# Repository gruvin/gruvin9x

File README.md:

# This project has been superseded by [openTx](https://github.com/opentx/opentx) and [Fr-Sky's Taranis](http://www.frsky-rc.com/product/pro.php?pro_id=113) RC Transmitter

## gruvin9x
### This outdated archive was recreated from [https://gruvin9x.googlecode.com/](https://gruvin9x.googlecode.com/) for historical reference and for the many still running gruvin9x boards or its dirivitives. A friendly shout out to you all! :-)

<h2>G9X v4.x BOARD (DISCONTINUED)</h2>

Why? Because there's much better things on the horizon -- we think. Trusted sources confirm the ongoing development of a Fr-Sky X9D transmitter, which we understand will be supporting open9x firmware form launch. The board will be ARM 32-bit based and is rumoured to be targeting sub-USD$100 retail -- complete with Fr-Sky 16-channel transmitter module, built in. If this all turns out to be true, then the complete radio will cost less than the G9X board (in the small qty's we can manage) whilst having all the same features and more. So we wait.

We simply don't know if demand for the G9X system will continue -- or not. Whilst orders seem to still be trickling in -- now even for blank boards (wow!) -- we don't expect that to last. Right or wrong, Gruvin made the choice, not to risk funds on another batch of G9X v4.2 boards. Was it the right choice? Have your say at <a href='http://9xforums.com/forum/viewforum.php?f=66'>9xforums.com</a>.<br>

<h2>We recommend openTx firmware</h2>

Please visit the [openTx website](http://open-tx.org) or the [openTx project on GitHub](https://github.com/opentx/opentx) for more information.

---

<h2>Gruvin9X Project Brief</h2>
<blockquote><i>First off, we especially wish to thank all the amazing original and ongoing work by</i>Thomas Husterer<i>of the <a href='http://code.google.com/p/th9x/'>th9x project</a>. A good number of other people have also contributed ideas, code and more to his, this and other related projects. THANK YOU all!</i></blockquote>

The gruvin9x project was originally forked from <code>er9x v1.1 r262</code> (<a href='http://code.google.com/p/er9x/source/browse/?r=262'>http://code.google.com/p/er9x/source/browse/?r=262</a>) which was based on a earlier version of the original th9x code. A huge amount effort was later put into the gruvin9x code base by contributor bsongis, of the <a href='http://open9x.googlecode.com'>open9x</a> and <a href='http://companion9x.googlecode.com'>companion9x</a> projects, which later became the sole point of focus for our custom hardware firmware support.<br>

<b>Highlights ...</b>
<ul><li><a href='wiki/About.md'>Project Wiki Documentation</a>
</li><li><a href='wiki/ReProgram.md'>Re-programming Your 9X Radio</a> -- firmware downloads, flashing, etc.<br>
</li><li><a href='wiki/PCB.md'>Custom Main Board Development</a> -- <b>upgrade your '9X controller board!</b></li></ul>

<h2>But what <i>is</i> it?</h2>
In short, this is an RC modeller/hacker's dream come true. We get to use your own custom firmware in our radios, adding features and making changes whenever we like and all (generally) at much lower cost than comparable commercial gear -- especially in terms of firmware features and programmability. We currently support any PPM transmitter module, with a focus on Fr-Sky two-way products, as well as DSM, DSM2 and DSMX 'retro-fitted' modules, usually salvaged from cheap 4-ch bind'n'fly models, as found on eBay.<br>

Open9x firmware is written and maintained by active RC modellers. It is mature, stable and very powerful. Based on th9x's 'multiplexer' implementation, it is arguably a little difficult to learn compared to other systems -- but is much more flexible. Open9x firmware is a significantly more powerful replacement for the comparatively simple default factory firmware that comes with the '9X radios.<br>

The <a href='wiki/PCB.md'>gruvin9x custom controller board</a> was developed using a larger version of the original Atmel AVR chip, to give us more RAM, firmware code space and more I/O connections for additional peripherals, such as telemetry data port, RTC/SD-card interface and more.<br>

If your existing transmitter doesn't do something you wish it would, chances are that open9x already does. If it doesn't, then put in a feature request and, if it makes sense to others, then the firmware will likely soon perform your new function.<br>

Both the open9x firmware and the companion9x (desktop) projects support our poplar <a href='wiki/PCB.md'>G9X v4 Custom Controller board</a>.<br>

<blockquote><i><b>Caveat</b>: Firmware is  half the story -- quality of hardware is not a given and should also be carefully considered. Whilst the build quality of most 9X radios seems just fine, there have been notable exceptions. We therefore strongly recommend that all firmware functions as well as internal radio soldering joints and physical gimbal assembly be carefully checked, before committing a 'cheap' 9X radio controlled aircraft to the skies. SAFETY FIRST!</i></blockquote>

The original <a href='http://code.google.com/p/th9x/'>TH9X project</a> was (and very much still is) about completely replacing the factory supplied operating system in the Turnigy/Eurgle/iMax/Fly-Sky/etc 9X Remote Control transmitter from China -- currently retailing for around USD$40 -- HOW, we do not know!<br>

From there, other projects then spawned (were forked forked) from TH9X, including ER9X and gruvin9x. More are likely to follow as different interest focuses emerge. In our case, the focus was originally on providing practical Fr-Sky telemetry support and more recently, the design and production of an <a href='PCB.md'>custom controller board</a>, to be a drop-in, upgrade replacement for the stock '9X system controller.<br>

There's more about gruvin9x on the <a href='wiki/About.md'>About</a> wiki page.<br>

<h3>Documentation</h3>

## Best Source of Information for openTx (June 2015)
Head over to <a href='http://www.open-tx.org/'>http://www.open-tx.org/</a>

For G9X hardware or historical information, please consult the <a href='wiki/About.md'>project wiki</a> in the first instance, as well as the <a href='firmware/doc'>firmwar/doc/ directory</a>  for ~~all currently available~~ archival gruvin9x documentation.<br>

<h3>Other '9X OS Replacements</h3>

There's also at least one other project taking on the same basic goal, but of completely different design and unrelated to the TH/ER/gruvin9X projects. It's named Radio Clone, can be found at <a href='http://radioclone.sourceforge.net/'>http://radioclone.sourceforge.net/</a> and is well worth checking out.<br>

<h2>Downloading gruvin9x Firmware and Flashing Your Radio</h2>

For details on installing new firmware into you Turnigy/iMax/Eurgle/etc 9X RC Radio, see the <a href='FlashGuide.md'>Flash Guide</a> wiki page.<br>

<h2>Getting the gruvin9x Source Code</h2>
See the <a href='wiki/CompilingFromSource.md'>Compiling from Source</a> wiki page.<br>

<h2>Get Involved!</h2>
An independent group maintain an, 'all things 9X' forum over at <a href='http://openrcforums.com'>http://openrcforums.com</a>. The forum caters to several different firmware projects, has a documentation wiki attached and is probably the most popular hang-out for '9X enthusiasts and much more besides. Frankly, it's freaking AMAZING! Go check it out.

## Gruvin9X Project Wiki</a>
(converted from old Google Code site)

* [About gruvin9x](wiki/About.md)
* [G9X Features](wiki/Features.md)
* [Screen Shots](wiki/Features.md)
* [General FAQ](wiki/FAQ.md)
* [Re-progamming Your Radio](wiki/ReProgram.md)
 * [Latest Stable Binaries](wiki/LatestRelease.md)
 * [Development Binaries](wiki/DevBinaries.md)
 * [Flashing Binary Versions](wiki/FlashGuide.md)
 * [Compiling from Source](wiki/CompilingFromSource.md)
 * [Make Options](wiki/MakeOptions.md)
* [Custom PCB (v4.x)](wiki/PCB.md)
 * [Custom Schematics](wiki/Circuitry.md)
 * [Build Your Own Board](wiki/PcbAssembly.md)
 * [SD Card Installation](wiki/SdcardBoard.md)
 * [9X Reference Data](wiki/TurnigyV2.md)
  * [Reference Images](wiki/ReferenceImages.md)
  * [V2 Circuit Schematic](wiki/SchematicV2.md)
  * *[v4.x Custom Board FAQ](wiki/V41FAQ.md)*
  * *[Get your own PCB made](wiki/PCBFab.md)*
* [USB Programmer](wiki/GProg.md)
* [Telemetry](wiki/Telemetry.md)
 * [Fr-Sky Support](wiki/FrSky.md)
 * [Fr-Sky Interfacing](wiki/FrskyInterfacing.md)
 * [Fr-Sky on your Mac](wiki/FrSkyTerminalOSX.md)
 * [Porting to ER9X](wiki/FrskyToER9X.md)
* [Donator Recognition](wiki/Recognition.md)
* [Random Notes](wiki/RandomNotes.md)
 * [AoA / LRI Notes/Ideas](wiki/AoA.md)
 * [Backlight Information](wiki/BackLight.md)
 * [eePe EEPROM file manager](wiki/eePe.md)
 * [PPM-in Compatibility (Hack)](wiki/PpmIn.md)
 * [Ni-Mh packs! Or not?](wiki/PowerCells.md)
 * [Repeat Delay](wiki/RepeatDelay.md)
 * [Speaker Upgrade](wiki/SpeakerReplacement.md)
 * [Voltage Averaging](wiki/VoltageAveraging.md)

## External Links
 * <a href="http://open-tx.org" rel="nofollow" style="font-size:2.0em"><b>openTx</b></a>
 * <a href='http://code.google.com/p/er9x/'>Original ER9X Project Home</a>
 * <a href='http://code.google.com/p/th9x/'>ORIGINAL, Original TH9X Project Home</a> "Respect!" :-D
 * <a href='http://sourceforge.net/apps/mediawiki/radioclone/'>Radio Clone Project</a> -- Something different and well worth checking out.
 * <a href='http://www.rcmodelreviews.com/tendollarbattery.shtml'>$10 Li-Ion Battery Pack Upgrade</a>
 * <a href="http://code.google.com/p/frsky-terminal/" rel="nofollow">FrSky Terminal (OS X)</a>
 * <a href="http://openpnp.org/wiki/index.php/Main_Page" rel="nofollow">OpenPnP</a>
 * <a href="http://www.rcgroups.com/forums/member.php?u=301789" rel="nofollow">Argos&#39;s &#39;9X Modd&#39;ing Blog</a>
 * <a href="http://code.google.com/p/er9x/" rel="nofollow">er9x</a>
 * <a href="http://code.google.com/p/th9x/" rel="nofollow">th9x</a>
 * <a href="http://radioclone.org/" rel="nofollow">radioclone</a>
 * <a href="http://9xforums.com/forum/" rel="nofollow">9X Forums</a>
 * <a href="http://companion9x.googlecode.com" rel="nofollow">companion9x</a>
 * <a href="http://www.fsf.org/about/what-is-free-software" rel="nofollow">What is &#39;free&#39; software?</a>

```

```
<h3>DISCLAIMER</h3>
Whilst the gruvin9x project owner(s) aim to provide as much help to as many Turnigy/iMax/Eurgle/etc '9X users as practical, any perceived enthusiasm on their part to lure people into using gruvin9x over any other version, would be erroneous. This project was originally created primarily for the author's own use -- and of course to 'give back' to the Open Source Community, as the <a href='http://www.gnu.org/licenses/gpl-2.0.html'>GNU General Public License (V2)</a> requests. Anyone is welcome to use this code according to said license, as is, where is and indeed to submit suggestions for changes, improvements, additions, etc. The author welcomes comments, constructive criticism, assistance and general feedback but accepts no responsibility for anything what-so-ever that use of any information contained on this website may or may not be claimed to cause. Use at your own risk. Any opinions offered by this internet resource are expressly, only opinions. (Any information claiming to be fact but not legally verified as fact in actuality, must of course be considered mere opinion, regardless of context.) All care is taken, but no responsibility is accepted for the level of accuracy of any information here or anywhere the author may post text, images, video, audio or other content. Any and all images, photographs, charts, lists or graphical representations of any kind are intended for educational or indicative purposes only and may or may not accurately represent any given subject, topic or fact at any given time. Indeed, any such depictions are subject to change at any time for any reason without notice. Any monetary figures, presented by whatever means, are for indicative, informational or educational purposes only and all such figures are subject to change at any time without notice. The use of sarcasm may or may not feature throughout this internet resource and other, related or linked media, and as such is intended purely as light-hearted humour. No responsibility is accepted for anything what-so-ever relating to perceived truths related to such believed communications. Reader/viewer/listener beware! Any views expressed by individuals other than project owner(s) may or may not agree with the projects goals, intentions or license and no responsibility is taken for any such view or views under any circumstance. Any views so interpreted as being those of the gruvin9x project owner(s) should be taken as potentially inaccurate and with the acceptance that any views, expressed or implied, are at all times subject to change without notice. This disclaimer falls within the above conditions, being itself subject to change at any time without notice. In light of the afore mentioned disclaimers, readers should take heed of the possibility that they may be, a) potentially crazy for reading this far in the first place and, b) that this disclaimer itself, though quite serious, is in part also intended for entertainment purposes. Etc, etc, blah blah. You know the drill. Love and peace to all! Now let's get on with it. :-D

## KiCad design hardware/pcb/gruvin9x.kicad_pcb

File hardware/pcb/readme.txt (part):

This PCB is a rework of Gruvin's V3.0 PCB to use the 100pin ATMega 2560. It was primarily done to enable the 
use of JTAG debugging and also to free up some pins for future fun. (Cam). Most of the work was done by Cam,
which has been just wonderful. Thanks Cam! (Gruvin)

============================
= Differences V4.1 to V4.2 =
============================

. All six (x4) push button switch holes enlarged to allow factory assembly, without manual adjustments to component legs.
. Changes made around Q2/Q3 pseudo RS-232 buffers to improve waveform profiles. R117 was added. Other resitros were reduced in value.

============================
= Differences V4.0 to V4.1 =
============================

. Switched PB0 and PB6 (PPM_OUT and IDL2_SW) assignment around to allow for a hardware PPM_OUT solution.
. After the above change we discovered we couldn't use PB0 (/SS) as an input for IDL2_SW.
  Unfortuantely when hardware SPI is used PB0 (/SS) can only be used for output, so we switched PB0 and PB4 (IDL2_SW and SD_CS)
  We now have:
  PIN         V4.0          V4.1            
  PB0 (/SS)   PPM_OUT   SD_CS
  PB4         SD_CS     IDL2_SW
  PB6 (OC1B)  IDL2_SW   PPM_OUT
. Switched the PPM_IN pull down resistor (R80) to pull up, worked better that way.
. Added components for a soft off switch.
. A few net name changes, Spare4 and Spare3 became Spare1\LED-BL-opt and Spare2\Vib-opt, and some net name changes for the soft off addition.
. In the move round for the soft off switch I mananged to add another decoupling cap around the CPU (C64)
. LED backlight fix. Needed NPN transistor to switch the P-FET.
. Changed the series LED backlight resistor to 200 ohms from 100 ohms, it looked better.
. Polarized caps are now indicated on the silkscreen.
. Jumper J4 graphic on schematic changed to show the config we are currently using as default.
. SDCard board connector moved to be more central, fits easier this way, at least for me.
. SDCard board also renamed to avoid confusion between the two versions.
. Up switch moved down 0.2mm.
. Addition of a fuse to the K5 LED back light header. We really need to implement a fuse to protect the whole board but without a
  total rip up it isn't going to happen. The fuse took the space of R103 which was removed, it was felt it was not needed.
. Broke the 3.3v rail out and a fused BATT+
. BOM also updated to reflect changes.

============================
= Differences V3.0 to V4.0 =
============================

Major
-----
* Replaced 64 pin AMega 2561 with 100 pin 2560
* Removed the 4066. Gruvin felt it bad for not offering enough protection to the CPU incase of user misconnects. So 
  it had to go. We now have seperate output buffer transistors to the module and the trainer jack. 
* Added a filter cap around Q1 to try and stop spurious switching when the buzzer sounds.
* Added voltage dividers to the four spare ADC pins, these may be used for monitoring individual Tx cell voltages,
  or anything, thought it useful to provide voltage dividers onboard.  
* Removed matrix for push buttons to make the board a true drop in replacement.  
* Added JTAG header
* Changed 10pin ISP header to 6pin
* Added breakout headers for spare pins, the whole of port L, half of port F (4x ADCs), and port H (inc. a second 
  serial port)
* Remaining 4 pins broken out to test point pads here and there.
* Switched the I2C interface to use hardware I2C pins 
* Switched the ADC usage from port F to port K to free up JTAG pins
* Added interfacing, connectors etc. for two rotary encoders as per Multiplex Evo sets (Hardware debouncing 
  with a little RC network). Added these on pins with interrupt triggers just in case needed.
* Switched pin for IDL_SW1 with Spare1 just to make routing easier
* Signals KEY_Y2 and KEY_Y3 have replaced the digital GND signals on the 9 pin headers that go to the pot gimbals 
  and trim switches. Because the trim buttons are now in a switch matrix, digi GND is no longer needed but the 
  matrix signals KEY_Y2 and KEY_Y3 are. On the V3 board these signals came out on a separate 2 pin header but this 
  can be avoided by doing this.
  ** NOTE ** The switch matrix requires a little mod/fix to operate correctly. On both of the horizontal 
  trim PCBs the trim switches are connected to analogue GND and not digi GND as they should be. In order for the 
  matrix to operate correctly we must remove the connection to analogue GND (by cutting PCB traces) and connect it 
  across to the digi GND point (now the KEY_Yn point) on the vertical trim board. 
  Pictures for this mod are in the .\Data Sheets\Switch Matrix Changes\ directory
* Added circuity to drive a vibrating motor for alarms etc. Have used a variable voltage regulator with enable signal
 (1.2v - 5.5v @ 500ma). This should hopefully allow a selection of motors to be used. Have also added a jumper 
 that either allows the Spare_2/PG5 signal or the PH3/OC4A PWM ouput to drive the enable on the regulator. I think 
 PWM control maybe an overkill but the option is there. Early indications show PS3 controller vibration motors 
 look good, they wedge in just fine in the bottom left of the back of the case (to the left of the battery 
 compartment). Got a copy ps3 wired controller from eBay for 6GBP. Contains two motors with differing weights, 
 either seems fine.
 Have tried driving the TPS77601 enable input with a PWM signal of around 250Hz while using one of the PS3 motors 
 and it seems fine. Have uped filter capacitors from the datasheet to try and keep noise generated low. The current
 combination of caps represent the lowest noise I have managed to get on both the motor side and the input side.
 
Minor
-----
* Added mounting holes into schematic so they don't disappear if you tell the netlist update to delete components 
  it can't find 
* Amalgamated the projects KiCAD libraries, and restructured their directories to better reflect KiCAD's own 
  library structure. (They confuse me less this way)

=======================================
= For reference V2.14 to V3.0 changes =
=======================================

* Change of speaker to PWM pin (provides MUCH cleaner tonnes, too.)
* Existing speaker output retained on original pin also -- this was in fact intended for vibrating motor (optionally.)
* Added breakout of I2C (This was more of a change to the SDcard interface)
* Added transistor in PPM_IN linen (Principal reason was for buffering/amplification.)
* Added breakout of Back Light signal, Vcc, and GND to 3 pin header
* Rearranged stick/trim switch interface wiring to remove awkward/stuffed-up cross-over bug. (This is a biggie!)
* Fix of reversed Collector and Emitter connections on Q3
* Small corrections to hole and switch positions. V2.14 was well within acceptable tolerances though.

=====================
= Component changes =
=====================
I renamed a few library parts that also exist in the standard KiCAD libraries to avoid confusion. 

These items are usually standard KiCAD parts that have been copied to the Gruvin library and tweaked a 
little for the needs of the project or to fix errors. These and only these parts have been given the 
_GRUVIN suffix on top of the normal KiCAD name. Original Gruvin library parts are just named normally.

I also edited a few parts.

The diffs are:

Footprints/Modules
------------------
SM0603        -> SM0603_GRUVIN         Silkscreen outline different
PIN_ARRAY_3X1 _> PIN_ARRAY_3X1_GRUVIN  Larger spacing and different 3D representation
PIN_ARRAY_3X2 -> PIN_ARRAY_3x2_GRUVIN  Bigger pads & didn't like 3D representation in std KiCAD part
PIN_ARRAY_4X2 -> PIN_ARRAY_4X2_GRUVIN  Bigger pads & no 3d rep
PIN_ARRAY_4X1 -> PIN_ARRAY_4X1_GRUVIN  Bigger pads & no 3d rep
PIN_ARRAY_5X2 -> PIN_ARRAY_5X2_GRUVIN  Bigger pads on 8 pins
SW_PUSH_6x4MM                          Bigger pads

Schematic components
--------------------
ATMEGA2560-A  -> ATMEGA2560-A_GRUVIN   Would you believe the standard KiCAD part has two power pins missing !
ATMEGA64      -> ATMEGA64_GRUVIN       Not sure, need to ask Bryan
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
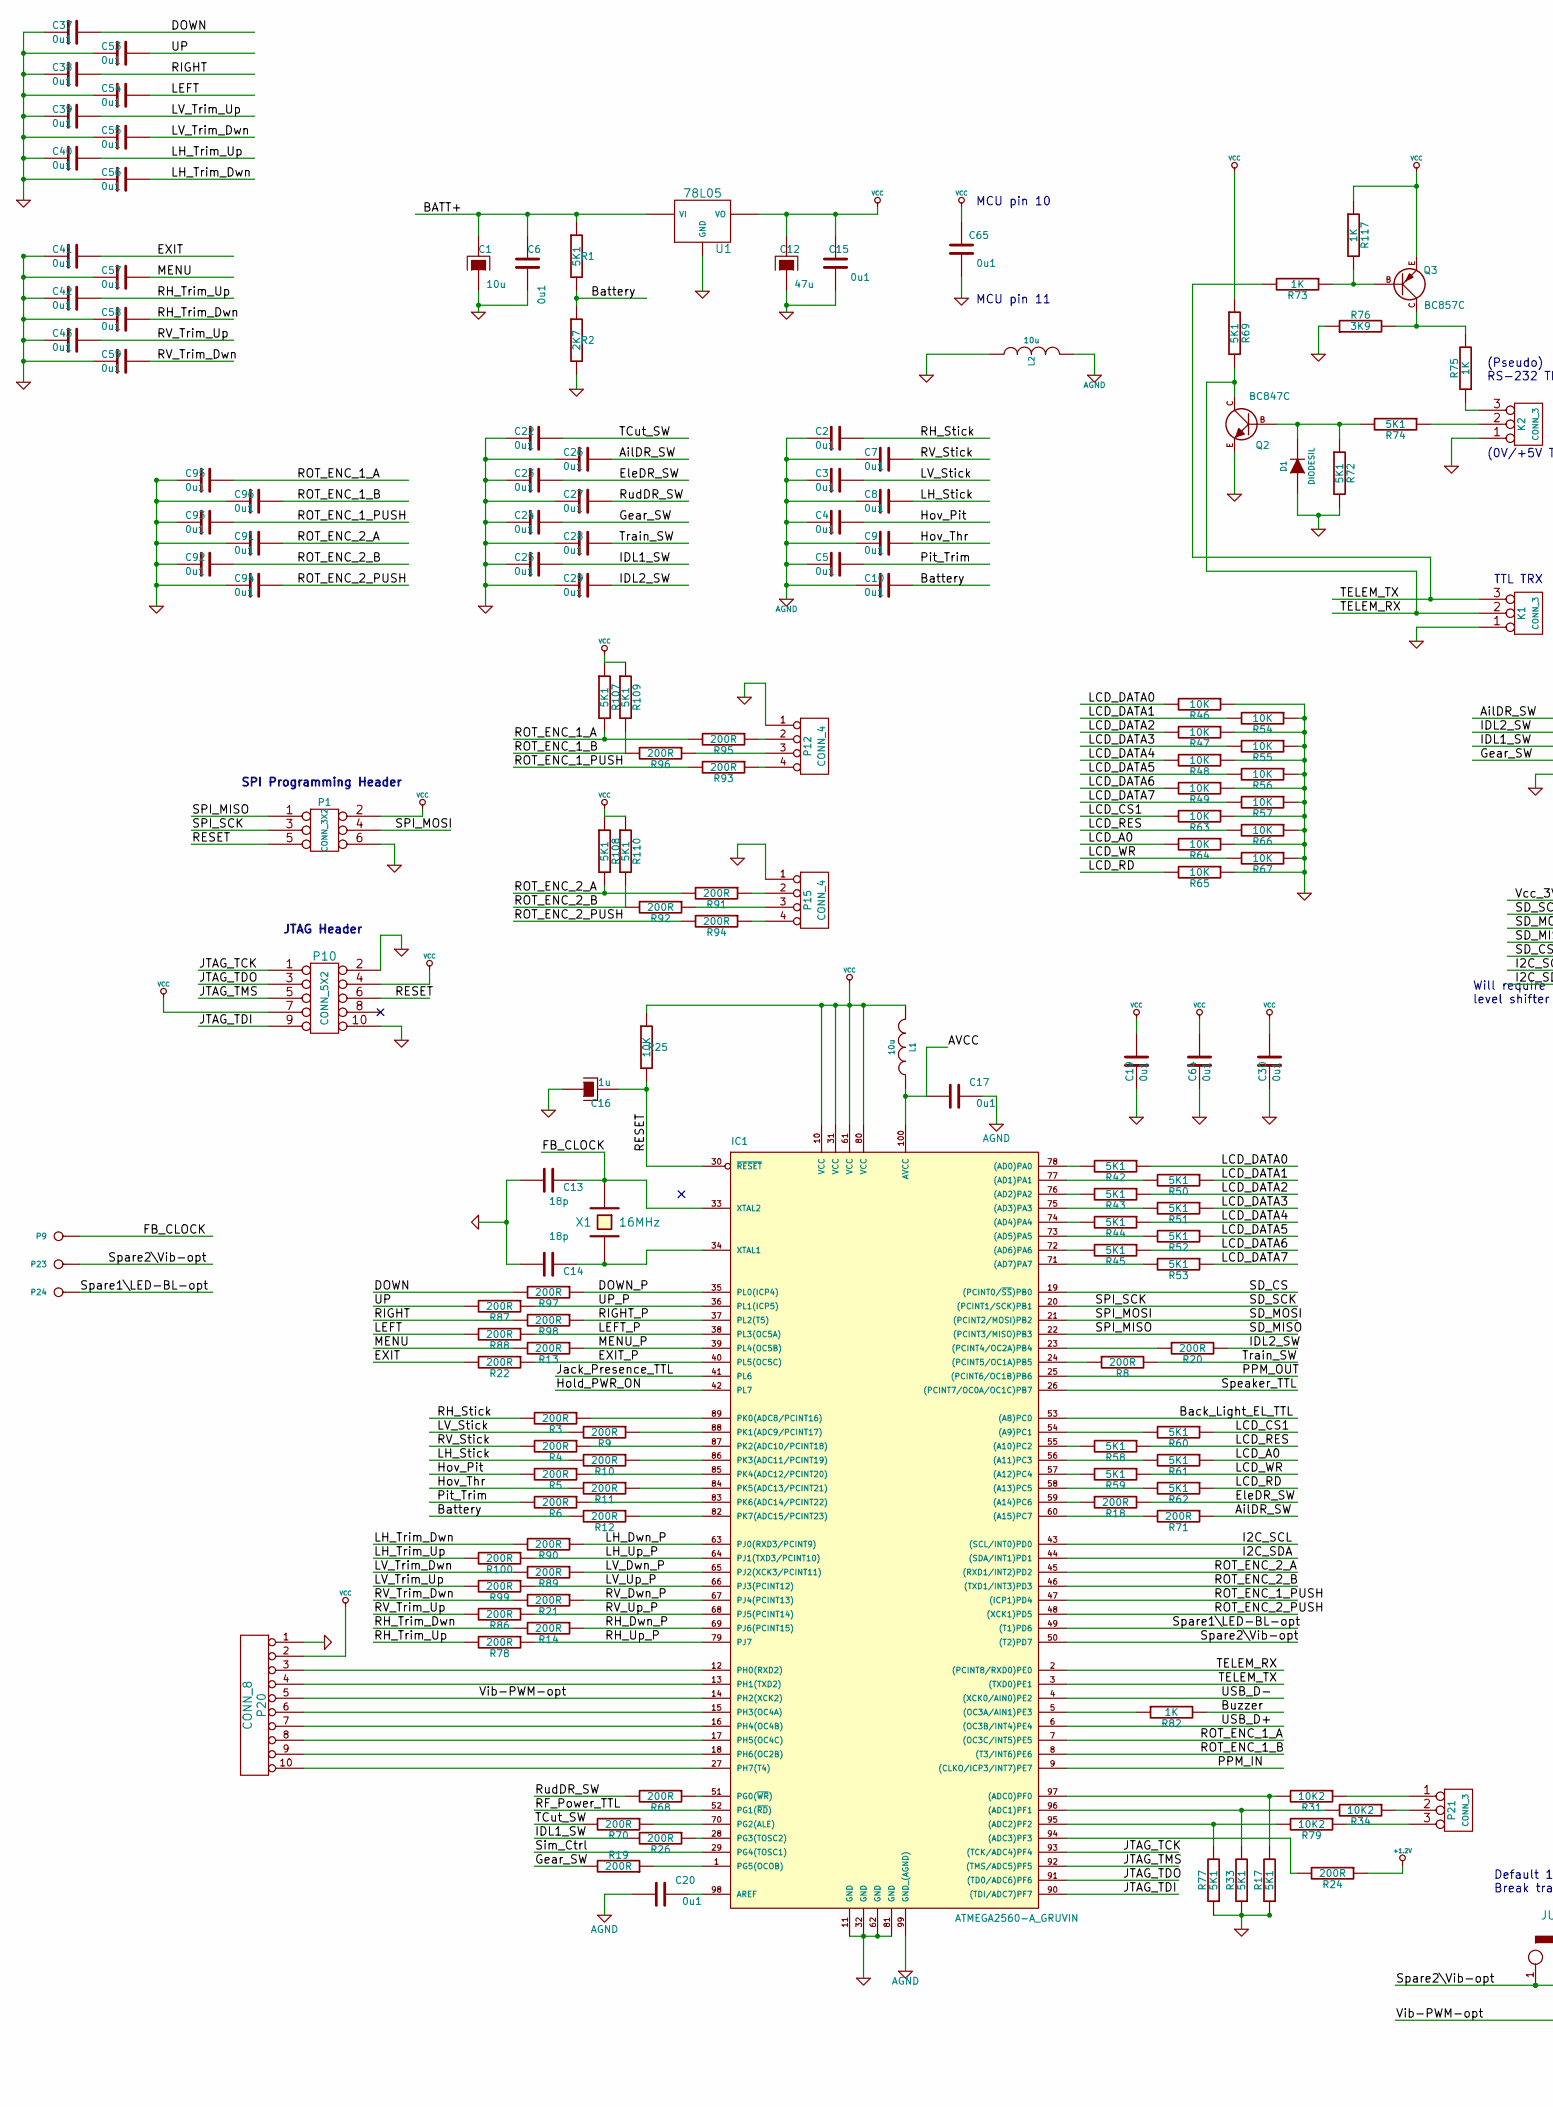
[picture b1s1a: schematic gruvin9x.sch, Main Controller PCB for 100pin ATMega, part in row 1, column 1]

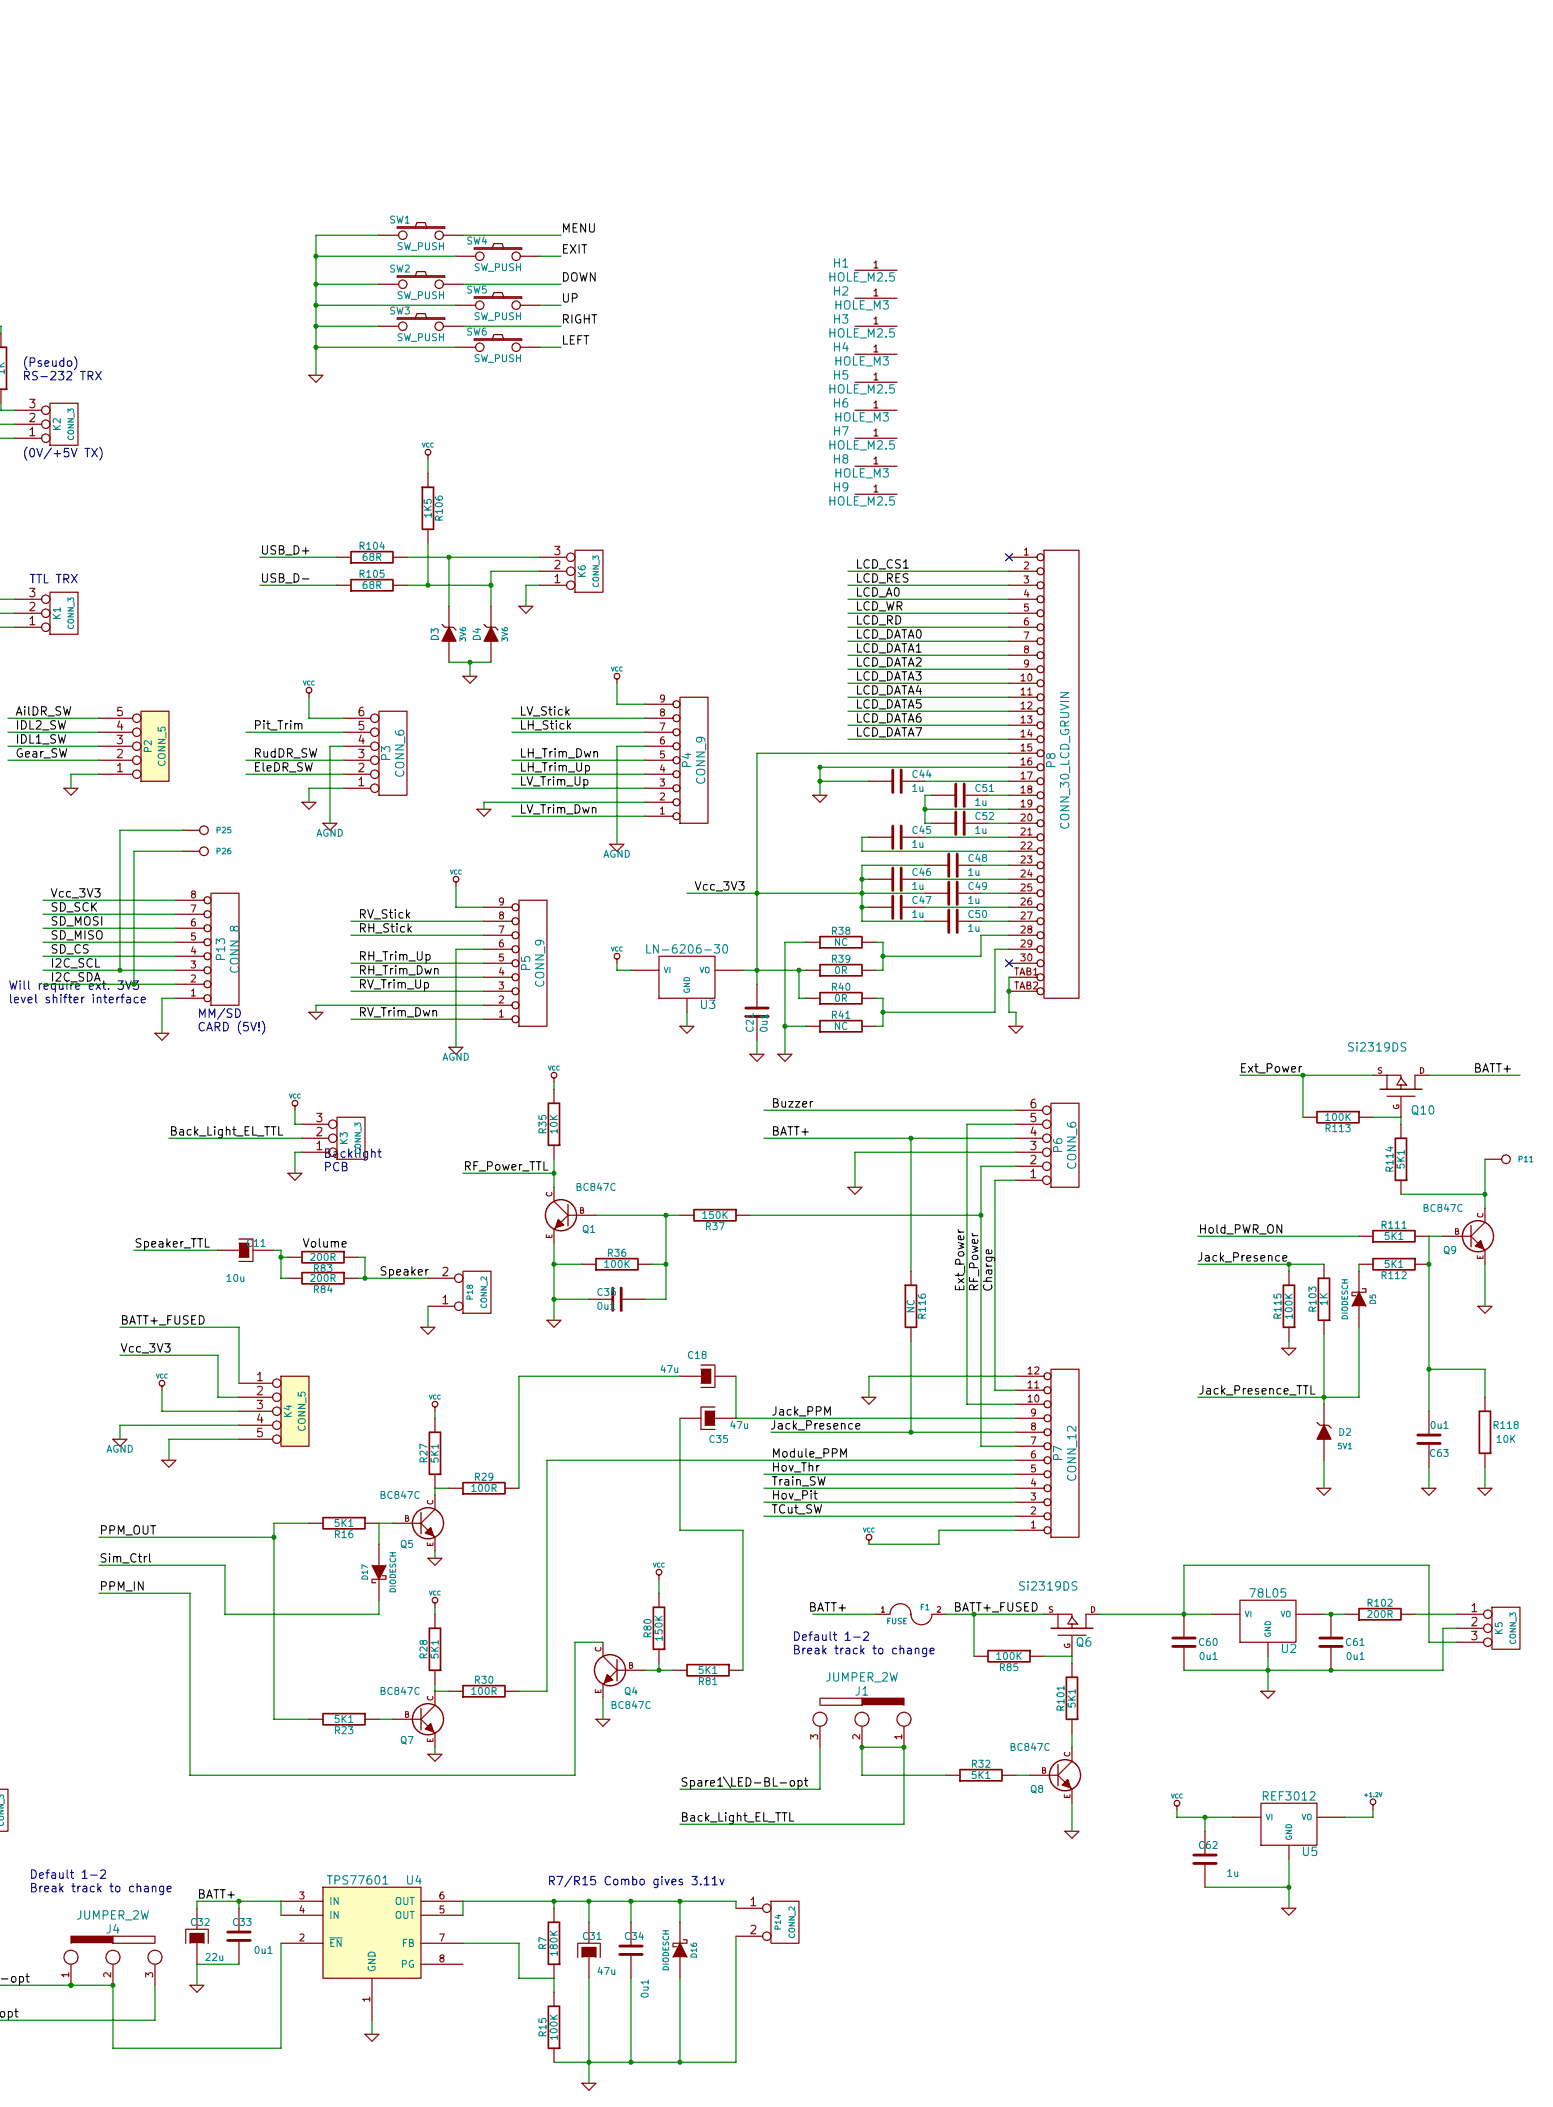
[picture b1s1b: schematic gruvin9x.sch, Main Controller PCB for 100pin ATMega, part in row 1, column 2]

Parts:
C1, C11: 10u
C2, C3, C4, C5, C6, C7, C8, C9, C10, C15, C17, C19, C20, C21, C22, C23, C24, C25, C26, C27, C28, C29, C30, C33, C34, C36, C37, C38, C39, C40, C41, C42, C43, C53, C54, C55, C56, C57, C58, C59, C60, C61, C63, C64, C65, C91, C92, C93, C94, C95, C96: 0u1
C12, C18, C31, C35: 47u
C13, C14: 18p
C16, C44, C45, C46, C47, C48, C49, C50, C51, C52, C62: 1u
C32: 22u
D1: DIODESIL
D2: 5V1
D3, D4: 3V6
D5, D16, D17: DIODESCH
F1: FUSE
H1, H3, H5, H7, H9: HOLE_M2.5
H2, H4, H6, H8: HOLE_M3
IC1: ATMEGA2560-A_GRUVIN; TQFP100
J1, J4: JUMPER_2W
K1, K2, K3, K5, K6: CONN_3
K4: CONN_5
L1, L2: 10u
P1: CONN_3X2
P2: CONN_5
P3, P6: CONN_6
P4, P5: CONN_9
P7: CONN_12
P8: CONN_30_LCD_GRUVIN
P9, P11, P23, P24, P25, P26: CONN_1
P10: CONN_5X2
P12, P15: CONN_4
P13, P20: CONN_8
P14: CONN_2
P18: CONN_2; CONN_2MM_2x1
P21: CONN_3
Q1, Q2, Q4, Q5, Q7, Q8, Q9: BC847C; SOT23-BCE
Q3: BC857C; SOT23-BCE
Q6, Q10: Si2319DS
R1, R16, R17, R23, R27, R28, R32, R33, R42, R43, R44, R45, R50, R51, R52, R53, R58, R59, R60, R61, R62, R69, R72, R74, R77, R81, R101, R107, R108, R109, R110, R111, R112, R114: 5K1
R2: 2K7
R3, R4, R5, R6, R8, R9, R10, R11, R12, R13, R14, R18, R19, R20, R21, R22, R24, R26, R68, R70, R71, R78, R83, R84, R86, R87, R88, R89, R90, R91, R92, R93, R94, R95, R96, R97, R98, R99, R100, R102: 200R
R7: 180K
R15, R36, R85, R113, R115: 100K
R25, R35, R46, R47, R48, R49, R54, R55, R56, R57, R63, R64, R65, R66, R67, R118: 10K
R29, R30: 100R
R31, R34, R79: 10K2
R37, R80: 150K
R38, R41, R116: NC
R39, R40: 0R
R73, R75, R82, R103, R117: 1K
R76: 3K9
R104, R105: 68R
R106: 1K5
SW1, SW2, SW3, SW4, SW5, SW6: SW_PUSH
U1, U2: 78L05; SOT89
U3: LN-6206-30; SOT89
U4: TPS77601
U5: REF3012; SOT89
X1: 16MHz

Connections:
+1.2V: R24.1, U5.VO
/AVCC: C17.2, IC1.100 (AVCC), L1.1
/AilDR_SW: C26.1, P2.5, R71.1
/BATT+: C1.2, C6.2, C32.2, C33.2, F1.1, P6.4, Q10.D, R1.1, R116.1, U1.VI, U4.3 (IN), U4.4 (IN)
/BATT+_FUSED: F1.2, K4.1, Q6.S, R85.2
/Back_Light_EL_TTL: IC1.53 ((A8)PC0), J1.1, J1.2, K3.2 (PM), R32.1
/Battery: C10.1, R1.2, R2.1, R12.2
/Buzzer: P6.6, R82.2
/Charge: P6.1, P7.11
/DOWN: C37.1, R97.2, SW2.1
/DOWN_P: IC1.35 (PL0(ICP4)), R97.1
/EXIT: C41.1, R22.2, SW4.1
/EXIT_P: IC1.40 (PL5(OC5C)), R22.1
/EleDR_SW: C23.1, P3.2, R18.2
/Ext_Power: P6.5, P7.10, Q10.S, R113.2
/FB_CLOCK: C13.1, IC1.33 (XTAL2), P9.1, X1.1
/Gear_SW: C24.1, P2.2, R19.2
/Hold_PWR_ON: IC1.42 (PL7), R111.1
/Hov_Pit: C4.1, P7.3, R5.2
/Hov_Thr: C9.1, P7.5, R11.2
/I2C_SCL: IC1.43 ((SCL/INT0)PD0), P13.3, P25.1
/I2C_SDA: IC1.44 ((SDA/INT1)PD1), P13.2, P26.1
/IDL1_SW: C25.1, P2.3, R26.2
/IDL2_SW: C29.1, P2.4, R20.2
/JTAG_TCK: IC1.93 ((TCK/ADC4)PF4), P10.1
/JTAG_TDI: IC1.90 ((TDI/ADC7)PF7), P10.9
/JTAG_TDO: IC1.91 ((TD0/ADC6)PF6), P10.3
/JTAG_TMS: IC1.92 ((TMS/ADC5)PF5), P10.5
/Jack_PPM: C18.2, C35.1, P7.9
/Jack_Presence: P7.8, R103.2, R115.2, R116.2
/Jack_Presence_TTL: D2.2 (K), D5.1 (A), IC1.41 (PL6), R103.1
/LCD_A0: P8.4, R61.1, R64.2
/LCD_CS1: P8.2, R60.1, R63.2
/LCD_DATA0: P8.7, R42.1, R46.2
/LCD_DATA1: P8.8, R50.1, R54.2
/LCD_DATA2: P8.9, R43.1, R47.2
/LCD_DATA3: P8.10, R51.1, R55.2
/LCD_DATA4: P8.11, R44.1, R48.2
/LCD_DATA5: P8.12, R52.1, R56.2
/LCD_DATA6: P8.13, R45.1, R49.2
/LCD_DATA7: P8.14, R53.1, R57.2
/LCD_RD: P8.6, R62.1, R65.2
/LCD_RES: P8.3, R58.1, R66.2
/LCD_WR: P8.5, R59.1, R67.2
/LEFT: C54.1, R88.2, SW6.1
/LEFT_P: IC1.38 (PL3(OC5A)), R88.1
/LH_Dwn_P: IC1.63 (PJ0(RXD3/PCINT9)), R90.1
/LH_Stick: C8.1, P4.7, R10.2
/LH_Trim_Dwn: C56.1, P4.5, R90.2
/LH_Trim_Up: C40.1, P4.4, R100.2
/LH_Up_P: IC1.64 (PJ1(TXD3/PCINT10)), R100.1
/LV_Dwn_P: IC1.65 (PJ2(XCK3/PCINT11)), R89.1
/LV_Stick: C3.1, P4.8, R9.2
/LV_Trim_Dwn: C55.1, P4.1, R89.2
/LV_Trim_Up: C39.1, P4.3, R99.2
/LV_Up_P: IC1.66 (PJ3(PCINT12)), R99.1
/MENU: C57.1, R13.2, SW1.1
/MENU_P: IC1.39 (PL4(OC5B)), R13.1
/Module_PPM: P7.6, R30.2
/PPM_IN: IC1.9 ((CLKO/ICP3/INT7)PE7), Q4.C
/PPM_OUT: IC1.25 ((PCINT6/OC1B)PB6), R16.2, R23.2
/Pit_Trim: C5.1, P3.5, R6.2
/RESET: C16.2, IC1.30 (~RESET), P1.5, P10.6, R25.2
/RF_Power: P6.2, P7.7, R37.1
/RF_Power_TTL: IC1.52 (PG1(~RD~)), Q1.C, R35.1
/RH_Dwn_P: IC1.69 (PJ6(PCINT15)), R14.1
/RH_Stick: C2.1, P5.7, R3.2
/RH_Trim_Dwn: C58.1, P5.4, R14.2
/RH_Trim_Up: C42.1, P5.5, R78.2
/RH_Up_P: IC1.79 (PJ7), R78.1
/RIGHT: C38.1, R98.2, SW3.1
/RIGHT_P: IC1.37 (PL2(T5)), R98.1
/ROT_ENC_1_A: C95.1, IC1.7 ((OC3C/INT5)PE5), R95.2, R107.2
/ROT_ENC_1_B: C96.1, IC1.8 ((T3/INT6)PE6), R96.2, R109.2
/ROT_ENC_1_PUSH: C93.1, IC1.47 ((ICP1)PD4), R93.2
/ROT_ENC_2_A: C91.1, IC1.45 ((RXD1/INT2)PD2), R91.2, R108.2
/ROT_ENC_2_B: C92.1, IC1.46 ((TXD1/INT3)PD3), R92.2, R110.2
/ROT_ENC_2_PUSH: C94.1, IC1.48 ((XCK1)PD5), R94.2
/RV_Dwn_P: IC1.67 (PJ4(PCINT13)), R21.1
/RV_Stick: C7.1, P5.8, R4.2
/RV_Trim_Dwn: C59.1, P5.1, R21.2
/RV_Trim_Up: C43.1, P5.3, R86.2
/RV_Up_P: IC1.68 (PJ5(PCINT14)), R86.1
/RudDR_SW: C27.1, P3.3, R68.2
/SD_CS: IC1.19 ((PCINT0/~SS~)PB0), P13.4
/SD_MISO: IC1.22 ((PCINT3/MISO)PB3), P1.1, P13.5
/SD_MOSI: IC1.21 ((PCINT2/MOSI)PB2), P1.4, P13.6
/SD_SCK: IC1.20 ((PCINT1/SCK)PB1), P1.3, P13.7
/Sim_Ctrl: D17.2 (K), IC1.29 (PG4(TOSC1))
/Spare1\LED-BL-opt: IC1.49 ((T1)PD6), J1.3, P24.1
/Spare2\Vib-opt: IC1.50 ((T2)PD7), J4.1, J4.2, P23.1, U4.2 (~EN)
/Speaker: P18.2 (PM), R83.1, R84.1
/Speaker_TTL: C11.1, IC1.26 ((PCINT7/OC0A/OC1C)PB7)
/TCut_SW: C22.1, P7.2, R70.2
/TELEM_RX: IC1.2 ((PCINT8/RXD0)PE0), K1.2 (PM), Q2.C, R69.2
/TELEM_TX: IC1.3 ((TXD0)PE1), K1.3, R73.2
/Train_SW: C28.1, P7.4, R8.2
/UP: C53.1, R87.2, SW5.1
/UP_P: IC1.36 (PL1(ICP5)), R87.1
/USB_D+: IC1.6 ((OC3B/INT4)PE4), R104.1
/USB_D-: IC1.4 ((XCK0/AIN0)PE2), R105.1
/Vcc_3V3: C21.1, C46.2, C47.2, C48.2, C49.2, C50.2, K4.2, P8.15, P13.8, R39.1, R40.1, U3.VO
/Vib-PWM-opt: IC1.14 (PH2(XCK2)), J4.3, P20.5
AGND: C2.2, C3.2, C4.2, C5.2, C7.2, C8.2, C9.2, C10.2, C17.1, C20.2, IC1.99 (GND_(AGND)), K4.4, L2.2, P3.4, P4.6, P5.6
GND: C1.1, C6.1, C12.1, C13.2, C14.2, C15.1, C16.1, C19.2, C21.2, C22.2, C23.2, C24.2, C25.2, C26.2, C27.2, C28.2, C29.2, C30.2, C31.1, C32.1, C33.1, C34.1, C36.2, C37.2, C38.2, C39.2, C40.2, C41.2, C42.2, C43.2, C44.2, C53.2, C54.2, C55.2, C56.2, C57.2, C58.2, C59.2, C60.1, C61.1, C62.1, C63.1, C64.2, C65.1, C91.2, C92.2, C93.2, C94.2, C95.2, C96.2, D1.1 (A), D2.1 (A), D3.1 (A), D4.1 (A), D16.1 (A), IC1.11 (GND), IC1.32 (GND), IC1.62 (GND), IC1.81 (GND), K1.1, K2.1, K3.1, K4.5, K5.2 (PM), K6.1, L2.1, P1.6, P2.1, P3.1, P4.2, P5.2, P6.3, P7.12, P8.16, P8.TAB1, P8.TAB2, P10.2, P10.10, P12.1, P13.1, P14.2 (PM), P15.1, P18.1, P20.1, Q1.E, Q2.E, Q4.E, Q5.E, Q7.E, Q8.E, Q9.E, R2.2, R15.1, R17.1, R33.1, R36.1, R38.1, R41.1, R46.1, R47.1, R48.1, R49.1, R54.1, R55.1, R56.1, R57.1, R63.1, R64.1, R65.1, R66.1, R67.1, R72.2, R76.1, R77.1, R115.1, R118.1, SW1.2, SW2.2, SW3.2, SW4.2, SW5.2, SW6.2, U1.GND, U2.GND, U3.GND, U4.1 (GND), U5.GND
unnamed: IC1.15 (PH3(OC4A)), P20.6
unnamed: IC1.13 (PH1(TXD2)), P20.4
unnamed: IC1.18 (PH6(OC2B)), P20.9
unnamed: IC1.27 (PH7(T4)), P20.10
unnamed: IC1.17 (PH5(OC4C)), P20.8
unnamed: IC1.16 (PH4(OC4B)), P20.7
unnamed: P12.4, R93.1
unnamed: P12.3, R96.1
unnamed: P12.2, R95.1
unnamed: C11.2, R83.2, R84.2
unnamed: P15.4, R94.1
unnamed: P15.3, R92.1
unnamed: P15.2, R91.1
unnamed: C61.2, R102.1, U2.VO
unnamed: Q6.G, R85.1, R101.2
unnamed: Q8.C, R101.1
unnamed: K5.1, R102.2
unnamed: R7.1, R15.2, U4.7 (FB)
unnamed: IC1.12 (PH0(RXD2)), P20.3
unnamed: IC1.5 ((OC3A/AIN1)PE3), R82.1
unnamed: C18.1, R29.2
unnamed: P21.1, R31.1
unnamed: P21.2 (PM), R34.1
unnamed: C31.2, C34.2, D16.2 (K), P14.1, R7.2, U4.5 (OUT), U4.6 (OUT)
unnamed: Q7.B, R23.1
unnamed: Q7.C, R28.1, R30.1
unnamed: D17.1 (A), Q5.B, R16.1
unnamed: Q5.C, R27.1, R29.1
unnamed: P8.29, R40.2, R41.2
unnamed: C44.1, P8.17
unnamed: C52.1, P8.20
unnamed: C45.2, P8.22
unnamed: C45.1, P8.21
unnamed: C48.1, P8.23
unnamed: C49.1, P8.25
unnamed: C46.1, P8.24
unnamed: C47.1, P8.26
unnamed: C50.1, P8.27
unnamed: C51.1, P8.18
unnamed: IC1.59 ((A14)PC6), R18.1
unnamed: IC1.1 (PG5(OCOB)), R19.1
unnamed: IC1.24 ((PCINT5/OC1A)PB5), R8.1
unnamed: IC1.23 ((PCINT4/OC2A)PB4), R20.1
unnamed: IC1.28 (PG3(TOSC2)), R26.1
unnamed: IC1.82 (PK7(ADC15/PCINT23)), R12.1
unnamed: IC1.83 (PK6(ADC14/PCINT22)), R6.1
unnamed: IC1.84 (PK5(ADC13/PCINT21)), R11.1
unnamed: IC1.86 (PK3(ADC11/PCINT19)), R10.1
unnamed: IC1.87 (PK2(ADC10/PCINT18)), R4.1
unnamed: IC1.88 (PK1(ADC9/PCINT17)), R9.1
unnamed: IC1.85 (PK4(ADC12/PCINT20)), R5.1
unnamed: IC1.89 (PK0(ADC8/PCINT16)), R3.1
unnamed: C14.1, IC1.34 (XTAL1), X1.2
unnamed: C20.1, IC1.98 (AREF)
unnamed: IC1.60 ((A15)PC7), R71.2
unnamed: IC1.58 ((A13)PC5), R62.2
unnamed: IC1.57 ((A12)PC4), R59.2
unnamed: IC1.56 ((A11)PC3), R61.2
unnamed: IC1.55 ((A10)PC2), R58.2
unnamed: IC1.54 ((A9)PC1), R60.2
unnamed: IC1.70 (PG2(ALE)), R70.1
unnamed: Q4.B, R80.1, R81.2
unnamed: C35.2, R81.1
unnamed: K2.2 (PM), R74.1
unnamed: IC1.51 (PG0(~WR~)), R68.1
unnamed: K2.3, R75.1
unnamed: IC1.75 ((AD3)PA3), R51.2
unnamed: IC1.74 ((AD4)PA4), R44.2
unnamed: IC1.73 ((AD5)PA5), R52.2
unnamed: IC1.72 ((AD6)PA6), R45.2
unnamed: IC1.71 ((AD7)PA7), R53.2
unnamed: C36.1, Q1.B, R36.2, R37.2
unnamed: IC1.76 ((AD2)PA2), R43.2
unnamed: IC1.77 ((AD1)PA1), R50.2
unnamed: IC1.78 ((AD0)PA0), R42.2
unnamed: P8.28, R38.2, R39.2
unnamed: C51.2, C52.2, P8.19
unnamed: Q10.G, R113.1, R114.2
unnamed: D5.2 (K), R112.2
unnamed: Q3.B, R73.1, R117.2
unnamed: D4.2 (K), K6.2 (PM), R105.2, R106.2
unnamed: D3.2 (K), K6.3, R104.2
unnamed: IC1.94 ((ADC3)PF3), R24.2
unnamed: Q8.B, R32.2
unnamed: C60.2, K5.3, Q6.D, U2.VI
unnamed: Q3.C, R75.2, R76.2
unnamed: P11.1, Q9.C, R114.1
unnamed: P21.3, R79.1
unnamed: C63.2, Q9.B, R111.2, R112.1, R118.2
unnamed: D1.2 (K), Q2.B, R72.1, R74.2
unnamed: IC1.95 ((ADC2)PF2), R77.2, R79.2
unnamed: IC1.96 ((ADC1)PF1), R33.2, R34.2
unnamed: IC1.97 ((ADC0)PF0), R17.2, R31.2
VCC: C12.2, C15.2, C19.1, C30.1, C62.2, C64.1, C65.2, IC1.10 (VCC), IC1.31 (VCC), IC1.61 (VCC), IC1.80 (VCC), K3.3, K4.3, L1.2, P1.2, P3.6, P4.9, P5.9, P7.1, P10.4, P10.7, P20.2, Q3.E, R25.1, R27.2, R28.2, R35.2, R69.1, R80.2, R106.1, R107.1, R108.1, R109.1, R110.1, R117.1, U1.VO, U3.VI, U5.VI

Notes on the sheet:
Default 1-2 Break track to change
MCU pin 11
MCU pin 10
R7/R15 Combo gives 3.11v
JTAG Header
Backlight PCB
Will require ext. 3V3 level shifter interface
MM/SD CARD (5V!)
(0V/+5V TX)
TTL TRX
(Pseudo) RS-232 TRX
SPI Programming Header

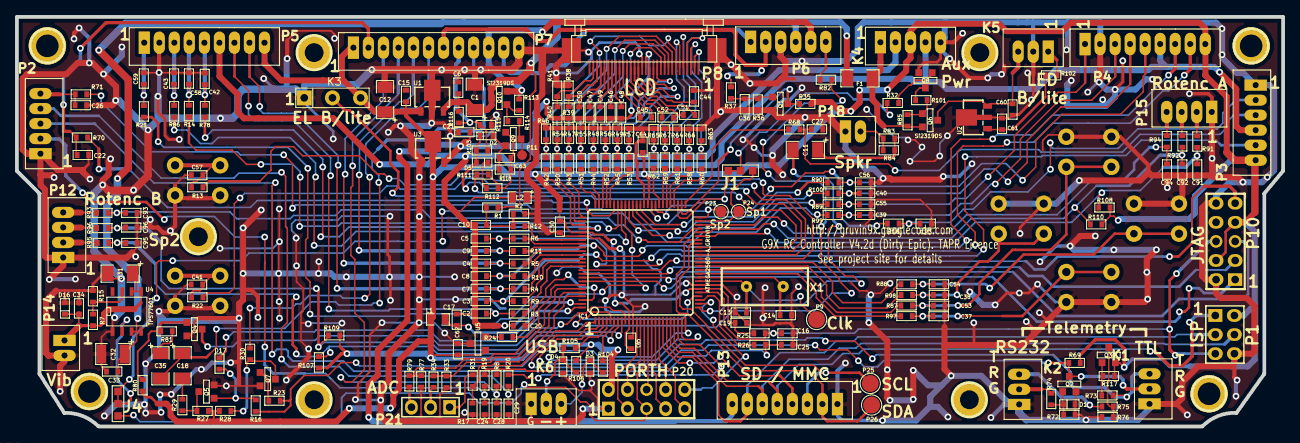
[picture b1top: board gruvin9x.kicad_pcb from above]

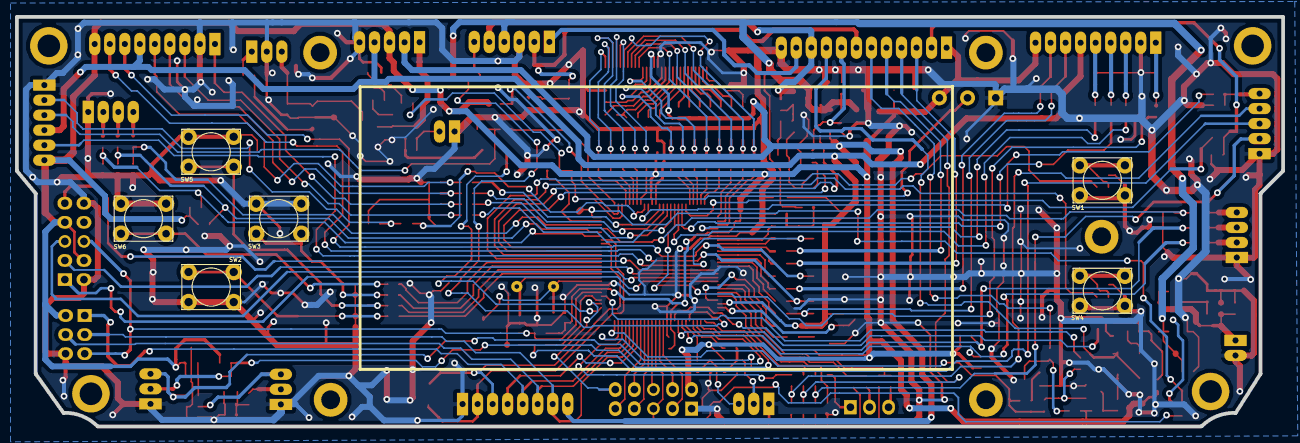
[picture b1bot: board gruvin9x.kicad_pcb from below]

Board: 2 copper layers, 168.5 x 54.5 mm, 261 parts (6 on the bottom side), 199 nets.

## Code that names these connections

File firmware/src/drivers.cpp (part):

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#  else

// Gruvin's PCBv2.14/v3 key scanning ...
#define KEY_Y0 1 // EXIT / MENU
#define KEY_Y1 2 // LEFT / RIGHT / UP / DOWN
#define KEY_Y2 4 // LV_Trim_Up / Down / LH_Trim_Up / Down 
#define KEY_Y3 8 // RV_Trim_Up / Down / RH_Trim_Up / Down 
#define TRIM_M_LH_DWN 0 // KEY_X0
#define TRIM_M_LH_UP  1 // KEY_X1
#define TRIM_M_LV_DWN 2 // KEY_X2
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
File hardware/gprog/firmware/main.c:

/*
 * USBasp - USB in-circuit programmer for Atmel AVR controllers
 *
 * Thomas Fischl <tfischl@gmx.de>
 *
 * License........: GNU GPL v2 (see Readme.txt)
 * Target.........: ATMega88 at 12 MHz
 * Creation Date..: 2005-02-20
 * Last change....: 2009-02-28
 *
 * PC2 SCK speed option.
 * GND  -> slow (8khz SCK),
 * open -> software set speed (default is 375kHz SCK)
 */

#include <avr/io.h>
#include <avr/interrupt.h>
#include <avr/pgmspace.h>
#include <avr/wdt.h>

#include "usbasp.h"
#include "usbdrv.h"
#include "isp.h"
#include "clock.h"

static uchar replyBuffer[8];

static uchar prog_state = PROG_STATE_IDLE;
static uchar prog_sck = USBASP_ISP_SCK_AUTO;

static uchar prog_address_newmode = 0;
static unsigned long prog_address;
static unsigned int prog_nbytes = 0;
static unsigned int prog_pagesize;
static uchar prog_blockflags;
static uchar prog_pagecounter;

static uchar isp_status = 0; // 1 = ISP connection established. Used to change green LED behaviour

uchar usbFunctionSetup(uchar data[8]) {

	uchar len = 0;

	if (data[1] == USBASP_FUNC_CONNECT) {

          /*
		// set SCK speed
		if ((PINC & (1 << PC2)) == 0) {
			ispSetSCKOption(USBASP_ISP_SCK_8);
		} else {
			ispSetSCKOption(prog_sck);
		}
          */
                ispSetSCKOption(prog_sck);

		/* set compatibility mode of address delivering */
		prog_address_newmode = 0;

		//ledGreenOn(); // it pulses on and off in idle mode, so make it on for sure here.
                isp_status = 1;
                bufferOn();
                while (--len); // delay
		ispConnect();
		ledRedOn();

	} else if (data[1] == USBASP_FUNC_DISCONNECT) {
		ispDisconnect();
                while (--len); // delay
                bufferOff();
		ledRedOff();
                isp_status = 0;

	} else if (data[1] == USBASP_FUNC_TRANSMIT) {
		replyBuffer[0] = ispTransmit(data[2]);
		replyBuffer[1] = ispTransmit(data[3]);
		replyBuffer[2] = ispTransmit(data[4]);
		replyBuffer[3] = ispTransmit(data[5]);
		len = 4;

	} else if (data[1] == USBASP_FUNC_READFLASH) {

		if (!prog_address_newmode)
			prog_address = (data[3] << 8) | data[2];

		prog_nbytes = (data[7] << 8) | data[6];
		prog_state = PROG_STATE_READFLASH;
		len = 0xff; /* multiple in */

	} else if (data[1] == USBASP_FUNC_READEEPROM) {

		if (!prog_address_newmode)
			prog_address = (data[3] << 8) | data[2];

		prog_nbytes = (data[7] << 8) | data[6];
		prog_state = PROG_STATE_READEEPROM;
		len = 0xff; /* multiple in */

	} else if (data[1] == USBASP_FUNC_ENABLEPROG) {
		replyBuffer[0] = ispEnterProgrammingMode();
		len = 1;

	} else if (data[1] == USBASP_FUNC_WRITEFLASH) {

		if (!prog_address_newmode)
			prog_address = (data[3] << 8) | data[2];

		prog_pagesize = data[4];
		prog_blockflags = data[5] & 0x0F;
		prog_pagesize += (((unsigned int) data[5] & 0xF0) << 4);
		if (prog_blockflags & PROG_BLOCKFLAG_FIRST) {
			prog_pagecounter = prog_pagesize;
		}
		prog_nbytes = (data[7] << 8) | data[6];
		prog_state = PROG_STATE_WRITEFLASH;
		len = 0xff; /* multiple out */

	} else if (data[1] == USBASP_FUNC_WRITEEEPROM) {

		if (!prog_address_newmode)
			prog_address = (data[3] << 8) | data[2];

		prog_pagesize = 0;
		prog_blockflags = 0;
		prog_nbytes = (data[7] << 8) | data[6];
		prog_state = PROG_STATE_WRITEEEPROM;
		len = 0xff; /* multiple out */

	} else if (data[1] == USBASP_FUNC_SETLONGADDRESS) {

		/* set new mode of address delivering (ignore address delivered in commands) */
		prog_address_newmode = 1;
		/* set new address */
		prog_address = *((unsigned long*) &data[2]);

	} else if (data[1] == USBASP_FUNC_SETISPSCK) {

		/* set sck option */
		prog_sck = data[2];
		replyBuffer[0] = 0;
		len = 1;
	}

	usbMsgPtr = replyBuffer;

	return len;
}

uchar usbFunctionRead(uchar *data, uchar len) {

	uchar i;

	/* check if programmer is in correct read state */
	if ((prog_state != PROG_STATE_READFLASH) && (prog_state
			!= PROG_STATE_READEEPROM)) {
		return 0xff;
	}

	/* fill packet */
	for (i = 0; i < len; i++) {
		if (prog_state == PROG_STATE_READFLASH) {
			data[i] = ispReadFlash(prog_address);
		} else {
			data[i] = ispReadEEPROM(prog_address);
		}
		prog_address++;
	}

	/* last packet? */
	if (len < 8) {
		prog_state = PROG_STATE_IDLE;
	}

	return len;
}

uchar usbFunctionWrite(uchar *data, uchar len) {

	uchar retVal = 0;
	uchar i;

	/* check if programmer is in correct write state */
	if ((prog_state != PROG_STATE_WRITEFLASH) && (prog_state
			!= PROG_STATE_WRITEEEPROM)) {
		return 0xff;
	}

	for (i = 0; i < len; i++) {

		if (prog_state == PROG_STATE_WRITEFLASH) {
			/* Flash */

			if (prog_pagesize == 0) {
				/* not paged */
				ispWriteFlash(prog_address, data[i], 1);
			} else {
				/* paged */
				ispWriteFlash(prog_address, data[i], 0);
				prog_pagecounter--;
				if (prog_pagecounter == 0) {
					ispFlushPage(prog_address, data[i]);
					prog_pagecounter = prog_pagesize;
				}
			}

		} else {
			/* EEPROM */
			ispWriteEEPROM(prog_address, data[i]);
		}

		prog_nbytes--;

		if (prog_nbytes == 0) {
			prog_state = PROG_STATE_IDLE;
			if ((prog_blockflags & PROG_BLOCKFLAG_LAST) && (prog_pagecounter
					!= prog_pagesize)) {

				/* last block and page flush pending, so flush it now */
				ispFlushPage(prog_address, data[i]);
			}

			retVal = 1; // Need to return 1 when no more data is to be received
		}

		prog_address++;
	}

	return retVal;
}

int main(void) {
        unsigned int pulseCounter;
        uchar i;

	/* no pullups on USB and ISP pins */
	PORTD = 0;
	PORTB = 0;
	///* all outputs except PD2 = INT0 */
	// DDRD = ~(1 << 2);
        // g: No -- ALL inputs. None of these pins are used

	/* all inputs except PC0(Red LED), PC1(Green LED) and PC3 (Buffer Enable) held low */
	DDRC = (1 << PC3) | (1 << PC1) | (1 << PC0);

        bufferOff(); // Buffer Enable PRC3 set to high-Z, with external pull-up

	/* output SE0 for USB reset */
	DDRB = 0x03;
        ledGreenOff();
	/* USB Reset by device only required on Watchdog Reset */
        i = 10;
        while (--i) {
          while (--pulseCounter)
          {
            if (pulseCounter & 0x8000) ledRedOff(); else ledRedOn();
          }
        }
	/* all USB and ISP pins inputs */
	DDRB = 0;

        ledRedOff();
        ledGreenOn();

	/* init timer */
	clockInit();

	/* main event loop */
	usbInit();
	sei();
	for (;;) {
		usbPoll();
                if (isp_status) ledGreenOn();
                else if (++pulseCounter & 0x8000) ledGreenOn(); else ledGreenOff();
                // wdt_reset();
	}
	return 0;
}

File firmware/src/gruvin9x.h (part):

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
#  define INP_G_Gear     5
#  define INP_G_ThrCt    2
#  define OUT_G_SIM_CTL  4 //1 : phone-jack=ppm_in
#  define INP_G_ID1      3
#  define INP_G_RF_POW   1
#  define INP_G_RuddDR   0
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#    define INP_C_AileDR  7
#  endif

#  define OUT_G_SIM_CTL  4 //1 : phone-jack=ppm_in
#  define INP_G_ID1      3
#  define INP_G_RF_POW   1
#  define INP_G_RuddDR   0
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// Hold_PWR_ON signal macros
#define set_pwr_on() (PORTL |= 0x80)
#define set_pwr_off() (PORTL &= ~0x80)
#define RF_Power (~PING & 0x02)
#define Jack_Presence (PINL & 0x40)

extern volatile uint8_t g_pdTimer;
extern uint8_t g_powerState;
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

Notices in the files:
firmware/src/drivers.cpp:
This program is free software; you can redistribute it and/or modify
it under the terms of the GNU General Public License version 2 as
published by the Free Software Foundation.
hardware/pcb/gruvin9x.kicad_pcb:
Licensed under the TAPR Open Hardware License (see file,  LICENSE)
Copyright 2011 th9xer
hardware/pcb/gruvin9x.sch:
Copyright 2011 C.Weeks
